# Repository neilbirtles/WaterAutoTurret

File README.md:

# Water Auto Turret

This is a fully automatic water turret that will track people and fire water at them. Intended to be a toy for children in the summer! Its constructed from a mix of 3D printed parts, aluminium extrusions and various other off the shelf items. The unit is powered by a 12v lead acid battery and plugs into a standard hosepipe push on connector for its water supply. It uses a Khadas VIM3 board to control everything and uses the onboard NPU to do the object tracking.

Full design information will be published here for those that want to make one for themselves

Current stage of development is:
    Mechanics: 90% complete, all functional items are working, just a few covers and minor parts need to be constructed
    Electronics: 95% complete, there are a couple of errors that need to be fixed in the rev2 PCB, but otherwise working
    Software: 50% complete, drivers and test code complete for the water control solenoids and stepper motors and an interface to YOLOv3 is implemented along with initial web front end

## Mechanics

All mechanical items have been designed in Fusion360 - model files to be published. 3D printed items have been printed on a Prusa Mk3S+

## Electronics

Main controller board is a Khadas VIM3. A custom PCB is used to interface to the Water Auto Turret. The PCB mounts a DRV8806 chip for driving 4 solenoids for controlling water flow to the turret, two Trinamic TMC5160 breakout boards for controlling the pitch and yaw stepper motors and some battery monitoring / power control circuitry

## Software 

Interface between the control electronics and the Khadas VIM3 is via WiringPi and SPI dev coded in python so should allow for porting to other SBC such as Raspberry Pi, but there will be obvious limitations for the object tracking if a board without an NPU is used. 

TMC5160_driver.py       - provides a generic TMC5160 driver written in python using WiringPi and SPIdev 
motor_test.py           - exercises the TMC5160 driver and allows both motors to be homed and then manually and automatically moved 

DRV8806_driver.py       - provides a driver for the DRV8806 chip written in python using WiringPi
solenoids_test.py       - exercises the DRV8806 driver and does a simple sequence of closing and opening the 4 valves 

KhadasYolov3Detector    - uses the Khadas Yolo v3 demo from here https://gitlab.com/khadas/aml_npu_app and adds in a simple TCP server to output the detections in JSON format to allow them to be used by the main python application 

Webserver               - initial outline of a flask web front end to provide control info for the water auto turret

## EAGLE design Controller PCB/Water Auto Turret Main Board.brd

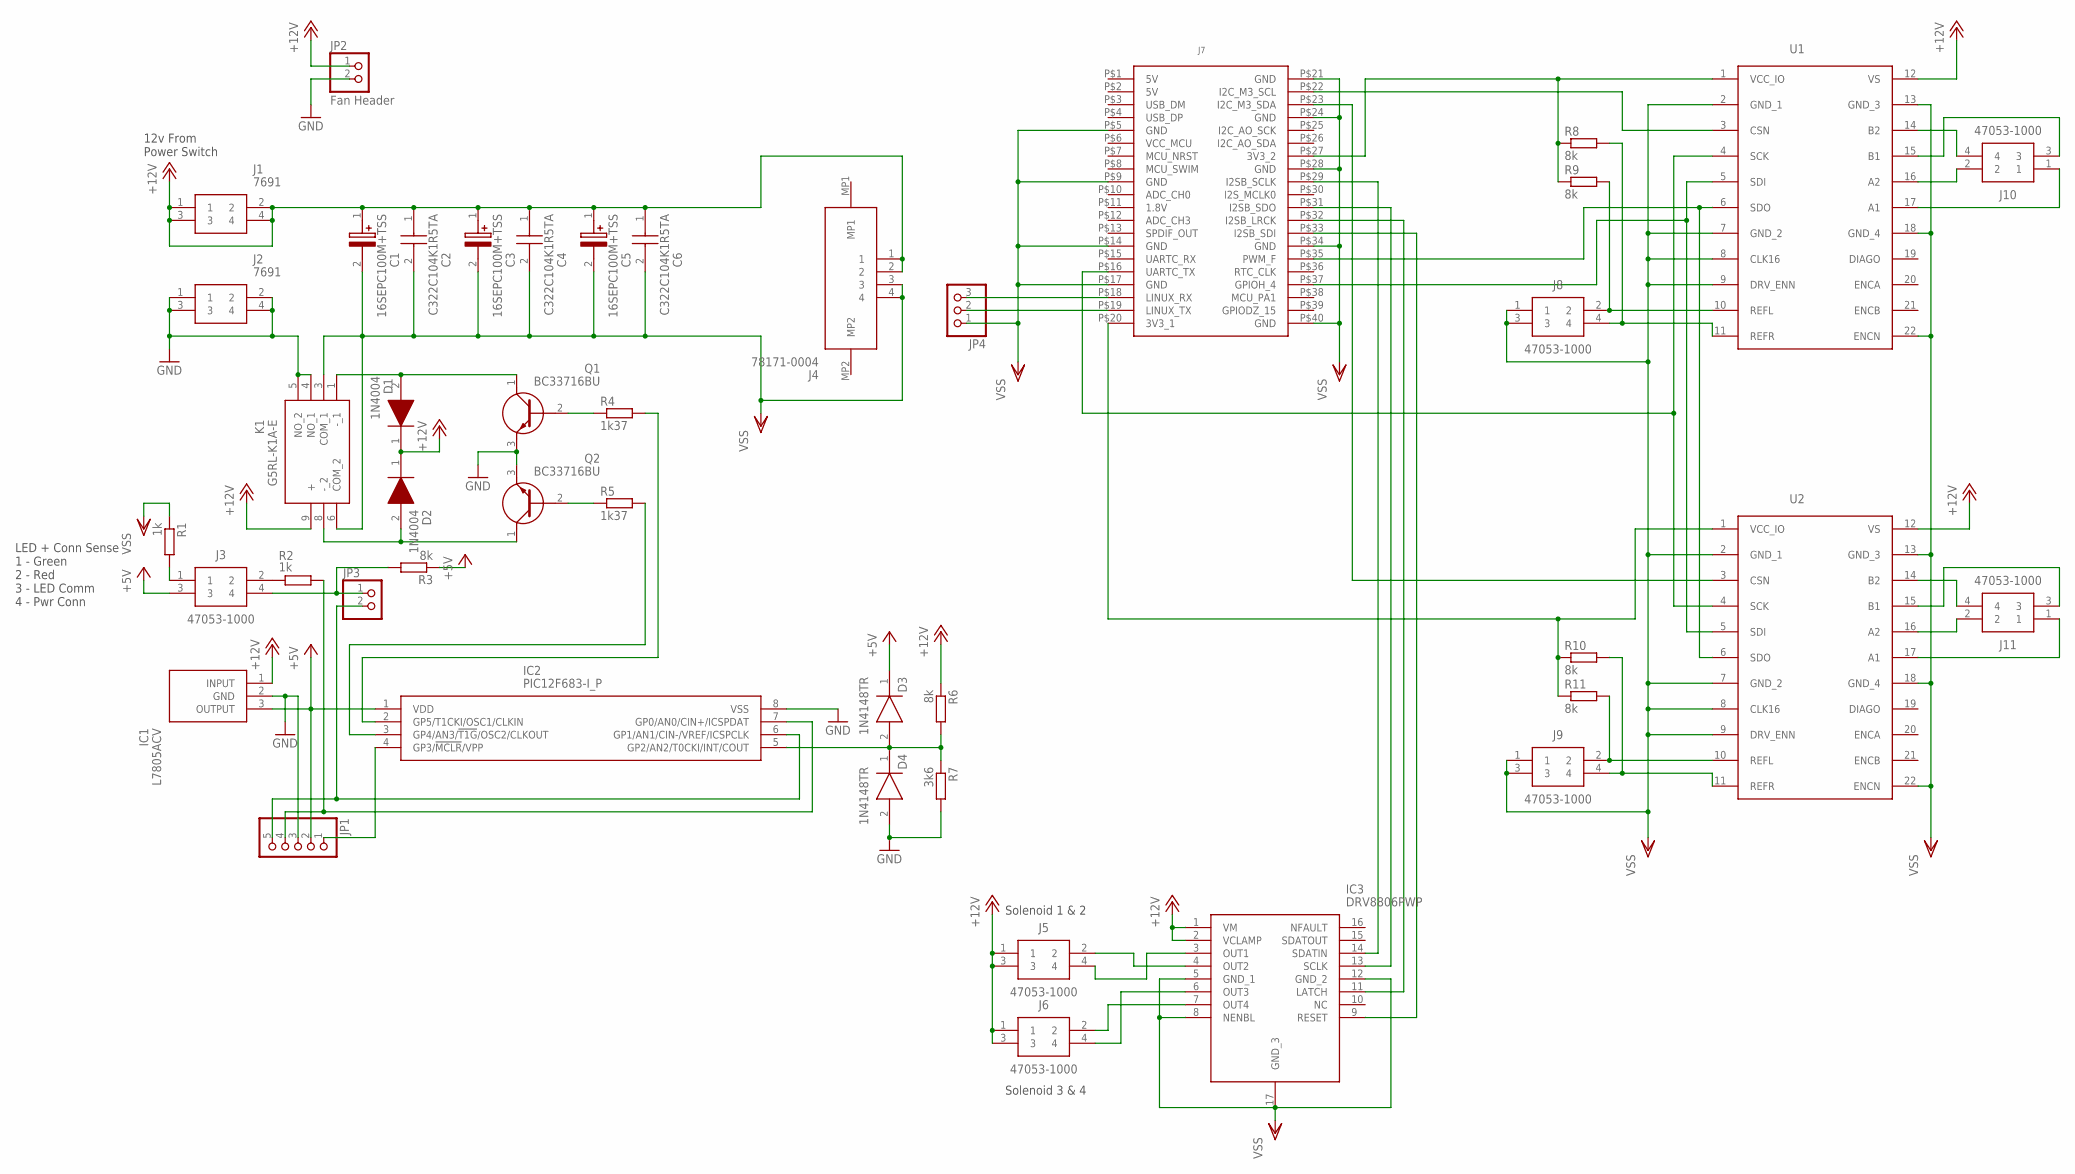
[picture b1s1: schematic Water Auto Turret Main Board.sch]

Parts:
C1, C3, C5: 16SEPC100M+TSS; CAPPRD250W45D630H600
C2, C4, C6: C322C104K1R5TA
D1, D2: 1N4004; DIOAD1408W86L464D236
D3, D4: 1N4148TR; DIOAD990W55L340D162
IC1: L7805ACV; TO255P460X1020X2008-3P
IC2: PIC12F683-I_P; DIP781W56P254L950H533Q8N
IC3: DRV8806PWP; SOP65P640X120-17N
J1, J2: 7691
J3, J6, J8, J9, J10, J11: 47053-1000
J4: 78171-0004; 781710004
J5: 47053-1000; MANUFACTURER_PART_NUMBER Solenoid 1 & 2
J7: VIM3GPIO
JP1: PINHD-1X5; 1X05
JP2: Fan Header; 1X02
JP3: PINHD-1X2; 1X02
JP4: PINHD-1X3; 1X03
K1: G5RL-K1A-E; G5RLK1AE
Q1, Q2: BC33716BU; TO-92
R1, R2: 1k; V234/12
R3: 8k; 0309V
R4, R5: 1k37; V234/12
R6, R8, R9, R10, R11: 8k; V234/12
R7: 3k6; 0309V
U1, U2: TMC5160-BOB

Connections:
5V: J7.P$1 (5V), J7.P$2 (5V)
+5V: D3.1 (K), IC1.3 (OUTPUT), IC2.1 (VDD), J3.3, JP1.2, R3.1
+12V: C1.1 (+), C2.1, C3.1 (+), C4.1, C5.1 (+), C6.1, D1.1 (K), D2.1 (K), IC1.1 (INPUT), IC3.1 (VM), IC3.2 (VCLAMP), J1.1, J1.2, J1.3, J1.4, J4.1, J4.2, J5.1, J5.3, J6.1, J6.3, JP2.1, K1.9 (+), R6.1, U1.12 (VS), U2.12 (VS)
GND: D4.2 (A), IC1.2 (GND), IC2.8 (VSS), J2.1, J2.2, J2.3, J2.4, JP1.3, JP2.2, K1.4 (NO_1), K1.5 (NO_2), Q1.3 (E), Q2.3 (E), R7.2
unnamed: IC3.4 (OUT2), J5.2
unnamed: IC3.3 (OUT1), J5.4
unnamed: IC3.6 (OUT3), J6.4
unnamed: IC3.7 (OUT4), J6.2
unnamed: J3.1, R1.2
unnamed: D1.2 (A), K1.1 (-_1), Q1.1 (C)
unnamed: D2.2 (A), K1.8 (-_2), Q2.1 (C)
unnamed: J3.2, R2.1
unnamed: IC2.4 (GP3/!MCLR!/VPP), JP1.1
unnamed: Q1.2 (B), R4.1
unnamed: IC2.7 (GP0/AN0/CIN+/ICSPDAT), JP1.4, R2.2
unnamed: IC2.6 (GP1/AN1/CIN-/VREF/ICSPCLK), JP1.5, JP3.2
unnamed: Q2.2 (B), R5.1
unnamed: IC2.3 (GP4/AN3/!T1G!/OSC2/CLKOUT), R5.2
unnamed: IC2.2 (GP5/T1CKI/OSC1/CLKIN), R4.2
unnamed: D3.2 (A), D4.1 (K), IC2.5 (GP2/AN2/T0CKI/INT/COUT), R6.2, R7.1
unnamed: J3.4, JP3.1, R3.2
unnamed: J7.P$35 (PWM_F), U1.6 (SDO), U2.6 (SDO)
unnamed: J7.P$37 (GPIOH_4), U1.5 (SDI), U2.5 (SDI)
unnamed: J7.P$16 (UARTC_TX), U1.4 (SCK), U2.4 (SCK)
unnamed: J10.4, U1.14 (B2)
unnamed: J10.3, U1.15 (B1)
unnamed: J10.1, U1.17 (A1)
unnamed: J10.2, U1.16 (A2)
unnamed: J11.4, U2.14 (B2)
unnamed: J11.2, U2.16 (A2)
unnamed: J11.1, U2.17 (A1)
unnamed: J11.3, U2.15 (B1)
unnamed: J8.2, R9.2, U1.10 (REFL)
unnamed: J8.4, R8.2, U1.11 (REFR)
unnamed: J9.2, R11.2, U2.10 (REFL)
unnamed: J9.4, R10.2, U2.11 (REFR)
unnamed: J7.P$20 (3V3_1), R10.1, R11.1, U2.1 (VCC_IO)
unnamed: IC3.14 (SDATIN), J7.P$29 (I2SB_SCLK)
unnamed: IC3.13 (SCLK), J7.P$31 (I2SB_SDO)
unnamed: IC3.11 (LATCH), J7.P$32 (I2SB_LRCK)
unnamed: IC3.9 (RESET), J7.P$33 (I2SB_SDI)
unnamed: J7.P$18 (LINUX_RX), JP4.3
unnamed: J7.P$19 (LINUX_TX), JP4.2
unnamed: J7.P$27 (3V3_2), R8.1, R9.1, U1.1 (VCC_IO)
unnamed: J7.P$22 (I2C_M3_SCL), U1.3 (CSN)
unnamed: J7.P$23 (I2C_M3_SDA), U2.3 (CSN)
VSS: C1.2 (-), C2.2, C3.2 (-), C4.2, C5.2 (-), C6.2, IC3.5 (GND_1), IC3.8 (NENBL), IC3.12 (GND_2), IC3.17 (GND_3), J4.3, J4.4, J7.P$5 (GND), J7.P$9 (GND), J7.P$14 (GND), J7.P$17 (GND), J7.P$21 (GND), J7.P$24 (GND), J7.P$28 (GND), J7.P$34 (GND), J7.P$40 (GND), J8.1, J8.3, J9.1, J9.3, JP4.1, K1.3 (COM_1), K1.6 (COM_2), R1.1, U1.2 (GND_1), U1.7 (GND_2), U1.8 (CLK16), U1.9 (DRV_ENN), U1.13 (GND_3), U1.18 (GND_4), U1.22 (ENCN), U2.2 (GND_1), U2.7 (GND_2), U2.8 (CLK16), U2.9 (DRV_ENN), U2.13 (GND_3), U2.18 (GND_4), U2.22 (ENCN)

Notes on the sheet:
Solenoid 1 & 2
Solenoid 3 & 4
12v From Power Switch
LED + Conn Sense 1 - Green 2 - Red 3 - LED Comm 4 - Pwr Conn

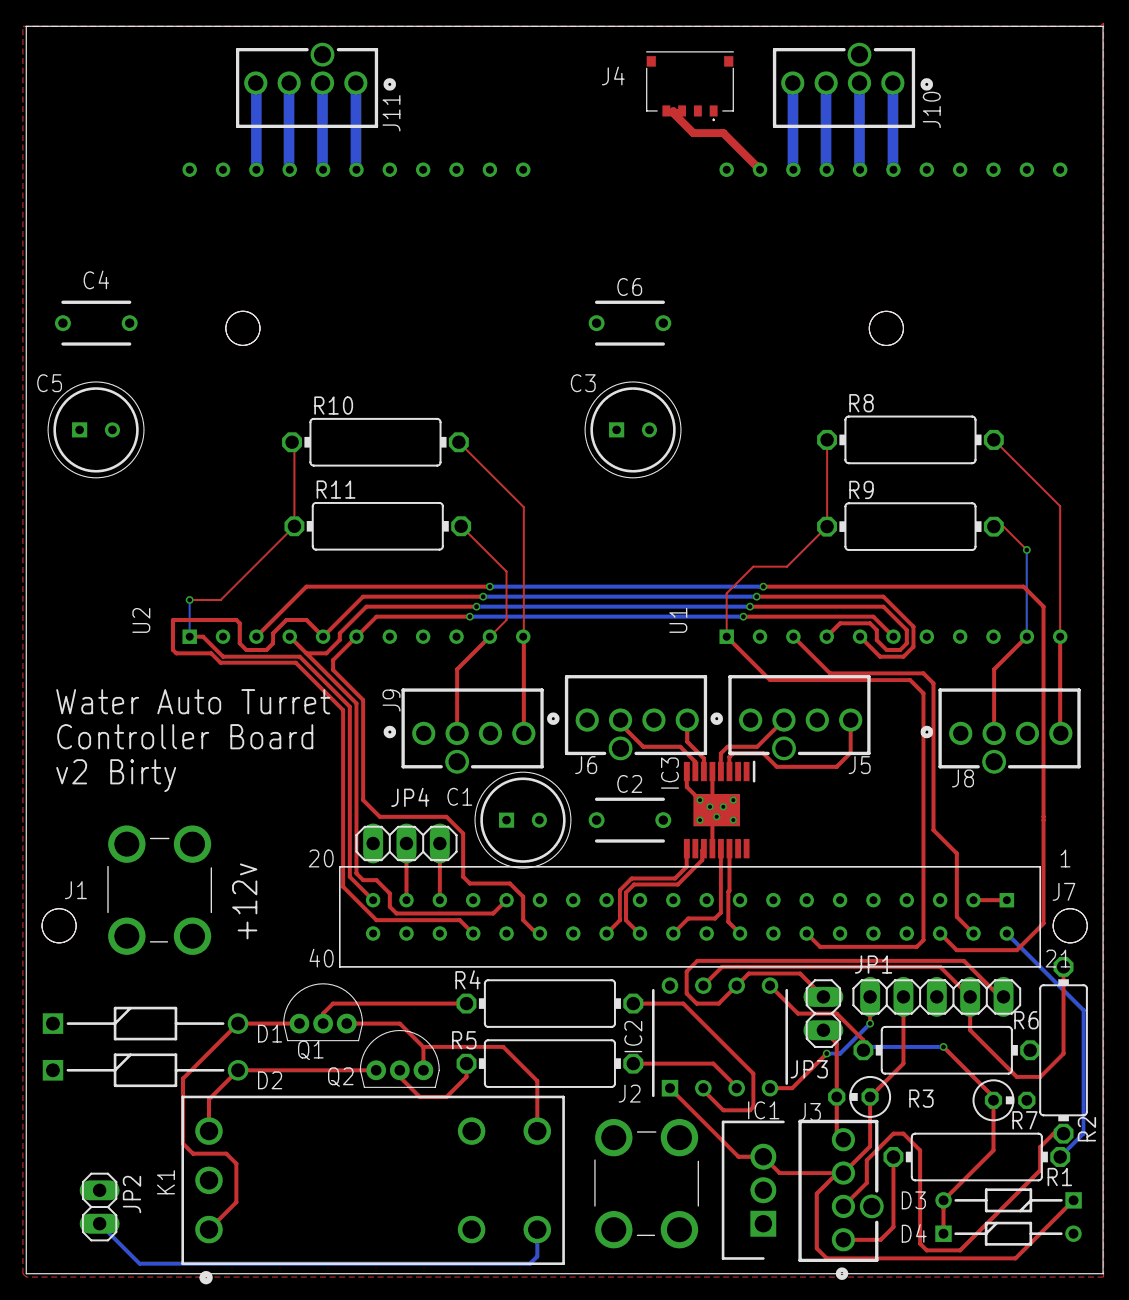
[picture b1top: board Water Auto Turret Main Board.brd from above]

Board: 2 copper layers, 82.0 x 95.0 mm, 44 parts (0 on the bottom side), 47 nets.

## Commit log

2021-06-19 Published Controller Board
2021-07-17 Solenoid and motor controller software and tests
2021-07-18 Moved files around to suit addition of web front end and added some initial info
2021-07-18 Added server to Khadas YOLOv3 demo to output detection information
2021-07-24 threading update
2021-07-27 Yolo i/f and turret move threads completed
2021-08-02 increase yaw motor current due to full mechanical load from pipework
2021-08-03 move to khadas python npu api, web frontend update
2021-08-09 working tracking and water control
2022-04-22 Set theme jekyll-theme-slate
2022-04-22 start of documentation
2022-05-03 Added 3D Printable Parts
2022-05-03 Added missing 3D printed profile joiner parts
2022-05-07 Rev2 PCB
    Fixes issues found on Rev1 PCB
2022-05-07 Firmware for controller board
2022-05-10 Images for documentation
2022-05-10 additional documentation images
2022-05-10 made backgrounds solid not transparent on images
2022-05-10 Fixed image links
2022-05-10 switch from index.md to README.md
2022-05-10 Code tidyup and alignment with latest khadas models
2022-05-10 removal of redundant code
2022-05-10 Documentation Upload
2022-05-10 fixed formatting and added back / next buttons
2022-05-10 Added 3D Model Export
2022-05-10 fixed navigation links
2022-05-15 Added BoM
